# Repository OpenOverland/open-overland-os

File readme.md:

# ESP32-based control board

Custom designed control board build around ESP32-S3 module.

### Specification:

1. Board dimensions: 130 x 70 mm, 4x M3-mounting holes (3.2mm inner diameter);
2. XT30 header as main Power-input (up to 15 Amps);
3. Blade-fuse holder on the board (in light-green color);
4. Designed around ESP32-S3-WROOM-1U module (external antenna needs to be attached to its I-PEX/u.FL connector);
5. 2x 6-pin Molex MicroFit 3.0 headers for a connection with the Locks;
6. 1x 4-pin Molex MicroFit 3.0 header for a connection with the 12V-RGB LED-strip;
7. A bunch of Horizontaly-oriented external JST-type connectors for digital and analog inputs, CAN, and RFID-module;
8. A few Vertically-oriented internal JST-type connectors for UART and I2C interfaces;
9. Communication with the RFID-module is over SPI (RC522 module considered by default).

### Main features:

- Overcurrent, overvoltage, reverse polarity protection;
- ESP32-S3 as MCU with the in-built Wi-Fi and Bluetooth capabilities;
- Controls 2x LOCKs (Southco R4-EM-9P15-150);
- 4 digital inputs (2 at board's edge), protected (optical insulation);
- 2 analog inputs (1 at board's edge), protected (ESD);
- 12V input power indication;
- CAN-bus interface with the 120-Ohm termination jumper (at board's edge);
- On-board RFID-module connector (at board's edge);
- Additional CAN-interface with the 120-Ohms termination jumper;
- Internal headers for I2C and UART interfaces;
- Battery voltage measurement circuit
- Transformed 3.3V power indication;
- Automotive-grade power supply (peak voltages resistant);
- 4-pin Molex MicroFit 3.0 connector for Addressable RGB LED-strip (WS2815 type only - 12V)

-------------

### RC522 vs. PN532

**RC522**

`Pros`

Very inexpensive (about 5$/pcs.).
Excellent for MIFARE Classic applications.
Easy to use.
Low power consumption.

`Cons`

Primarily supports ISO14443A.
No NFC functionality.
*Shorter reading distance.*
Many low-cost modules use poorly tuned antennas, reducing performance.

**PN532**

`Pros`

Full-featured NFC controller.
Supports all three NFC operating modes:
RFID/NFC Reader
Card Emulation
Peer-to-Peer
Compatible with Android smartphones.
Supports a wider variety of RFID/NFC card types.
*Generally offers better sensitivity and longer read range.*
Most breakout boards allow selecting SPI, I²C, or UART via jumpers or switches.

`Cons`

More expensive (about 8$/pcs.).
Slightly more complex to integrate.
*Higher power consumption.*

-------------

### Version history

**v2a**
This version is designed for each door (2x locks only)

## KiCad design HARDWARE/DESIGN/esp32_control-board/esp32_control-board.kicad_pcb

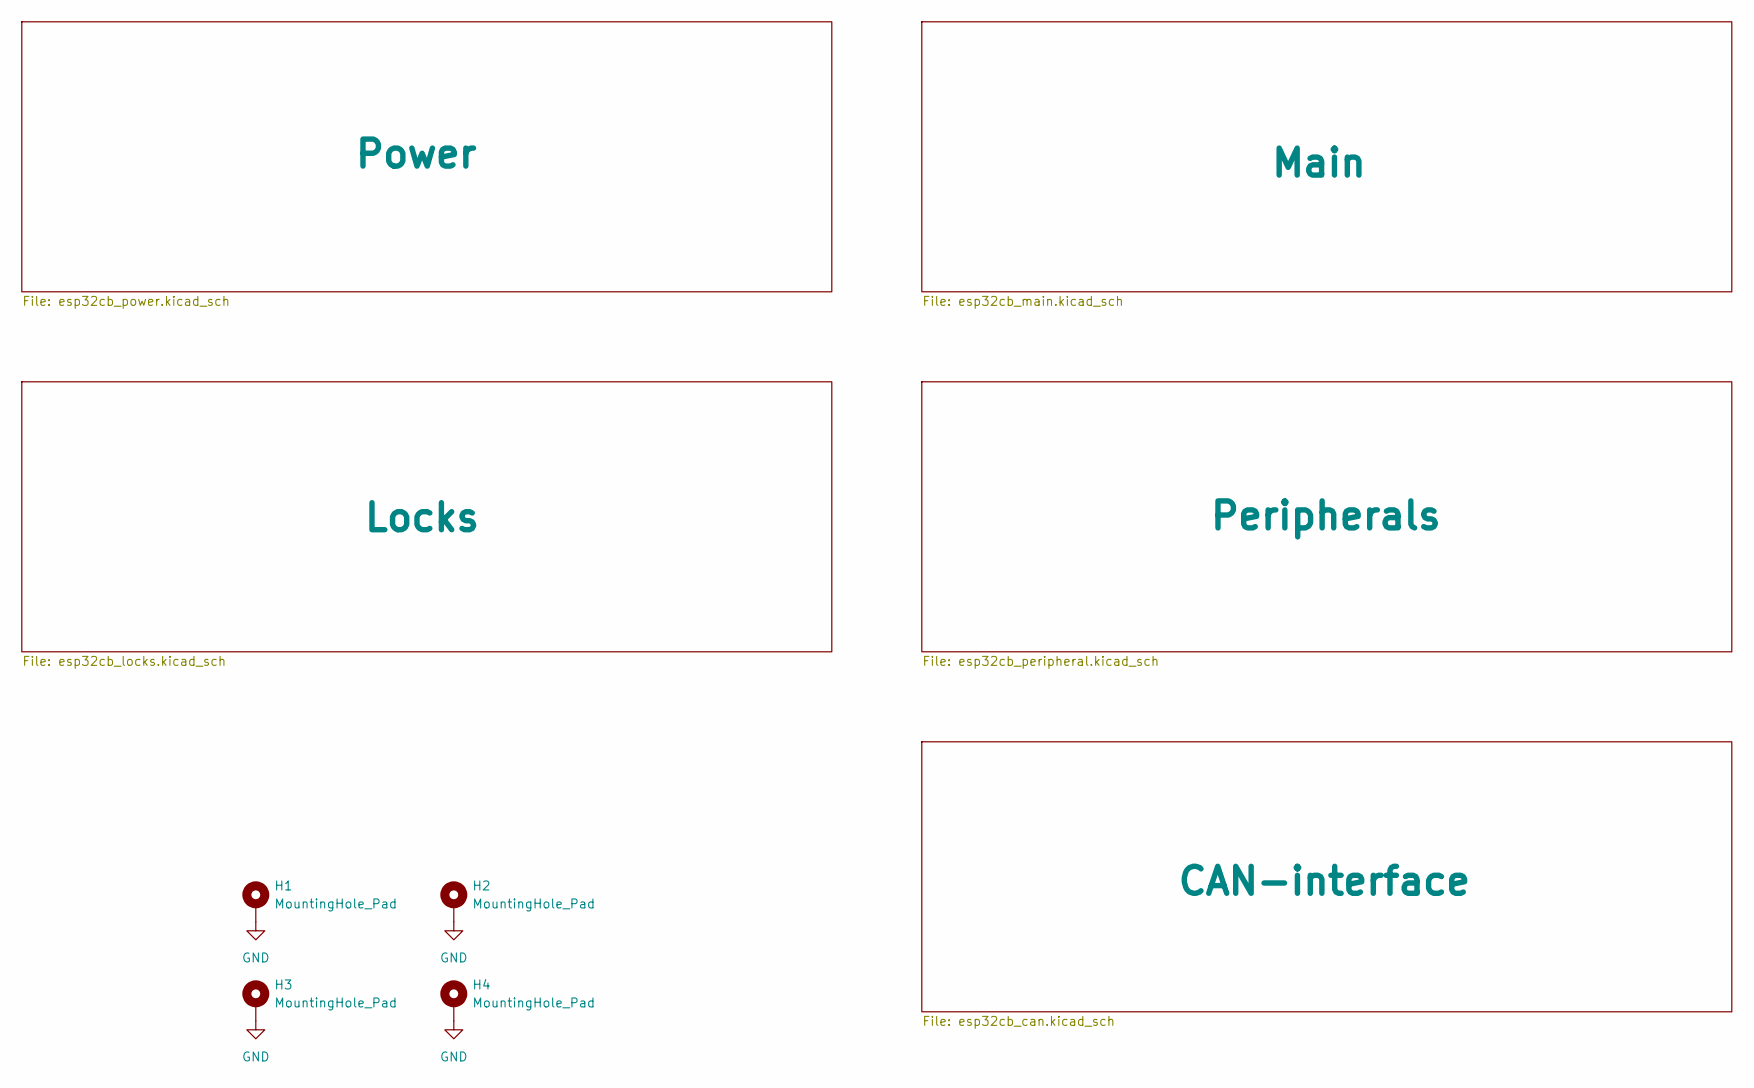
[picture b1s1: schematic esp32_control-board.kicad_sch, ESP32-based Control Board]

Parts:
H1, H2, H3, H4: MountingHole_Pad; MountingHole_3.2mm_M3_DIN965_Pad_TopBottom

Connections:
GND: H1.1 (1_1), H2.1 (1_1), H3.1 (1_1), H4.1 (1_1); also elsewhere on the board

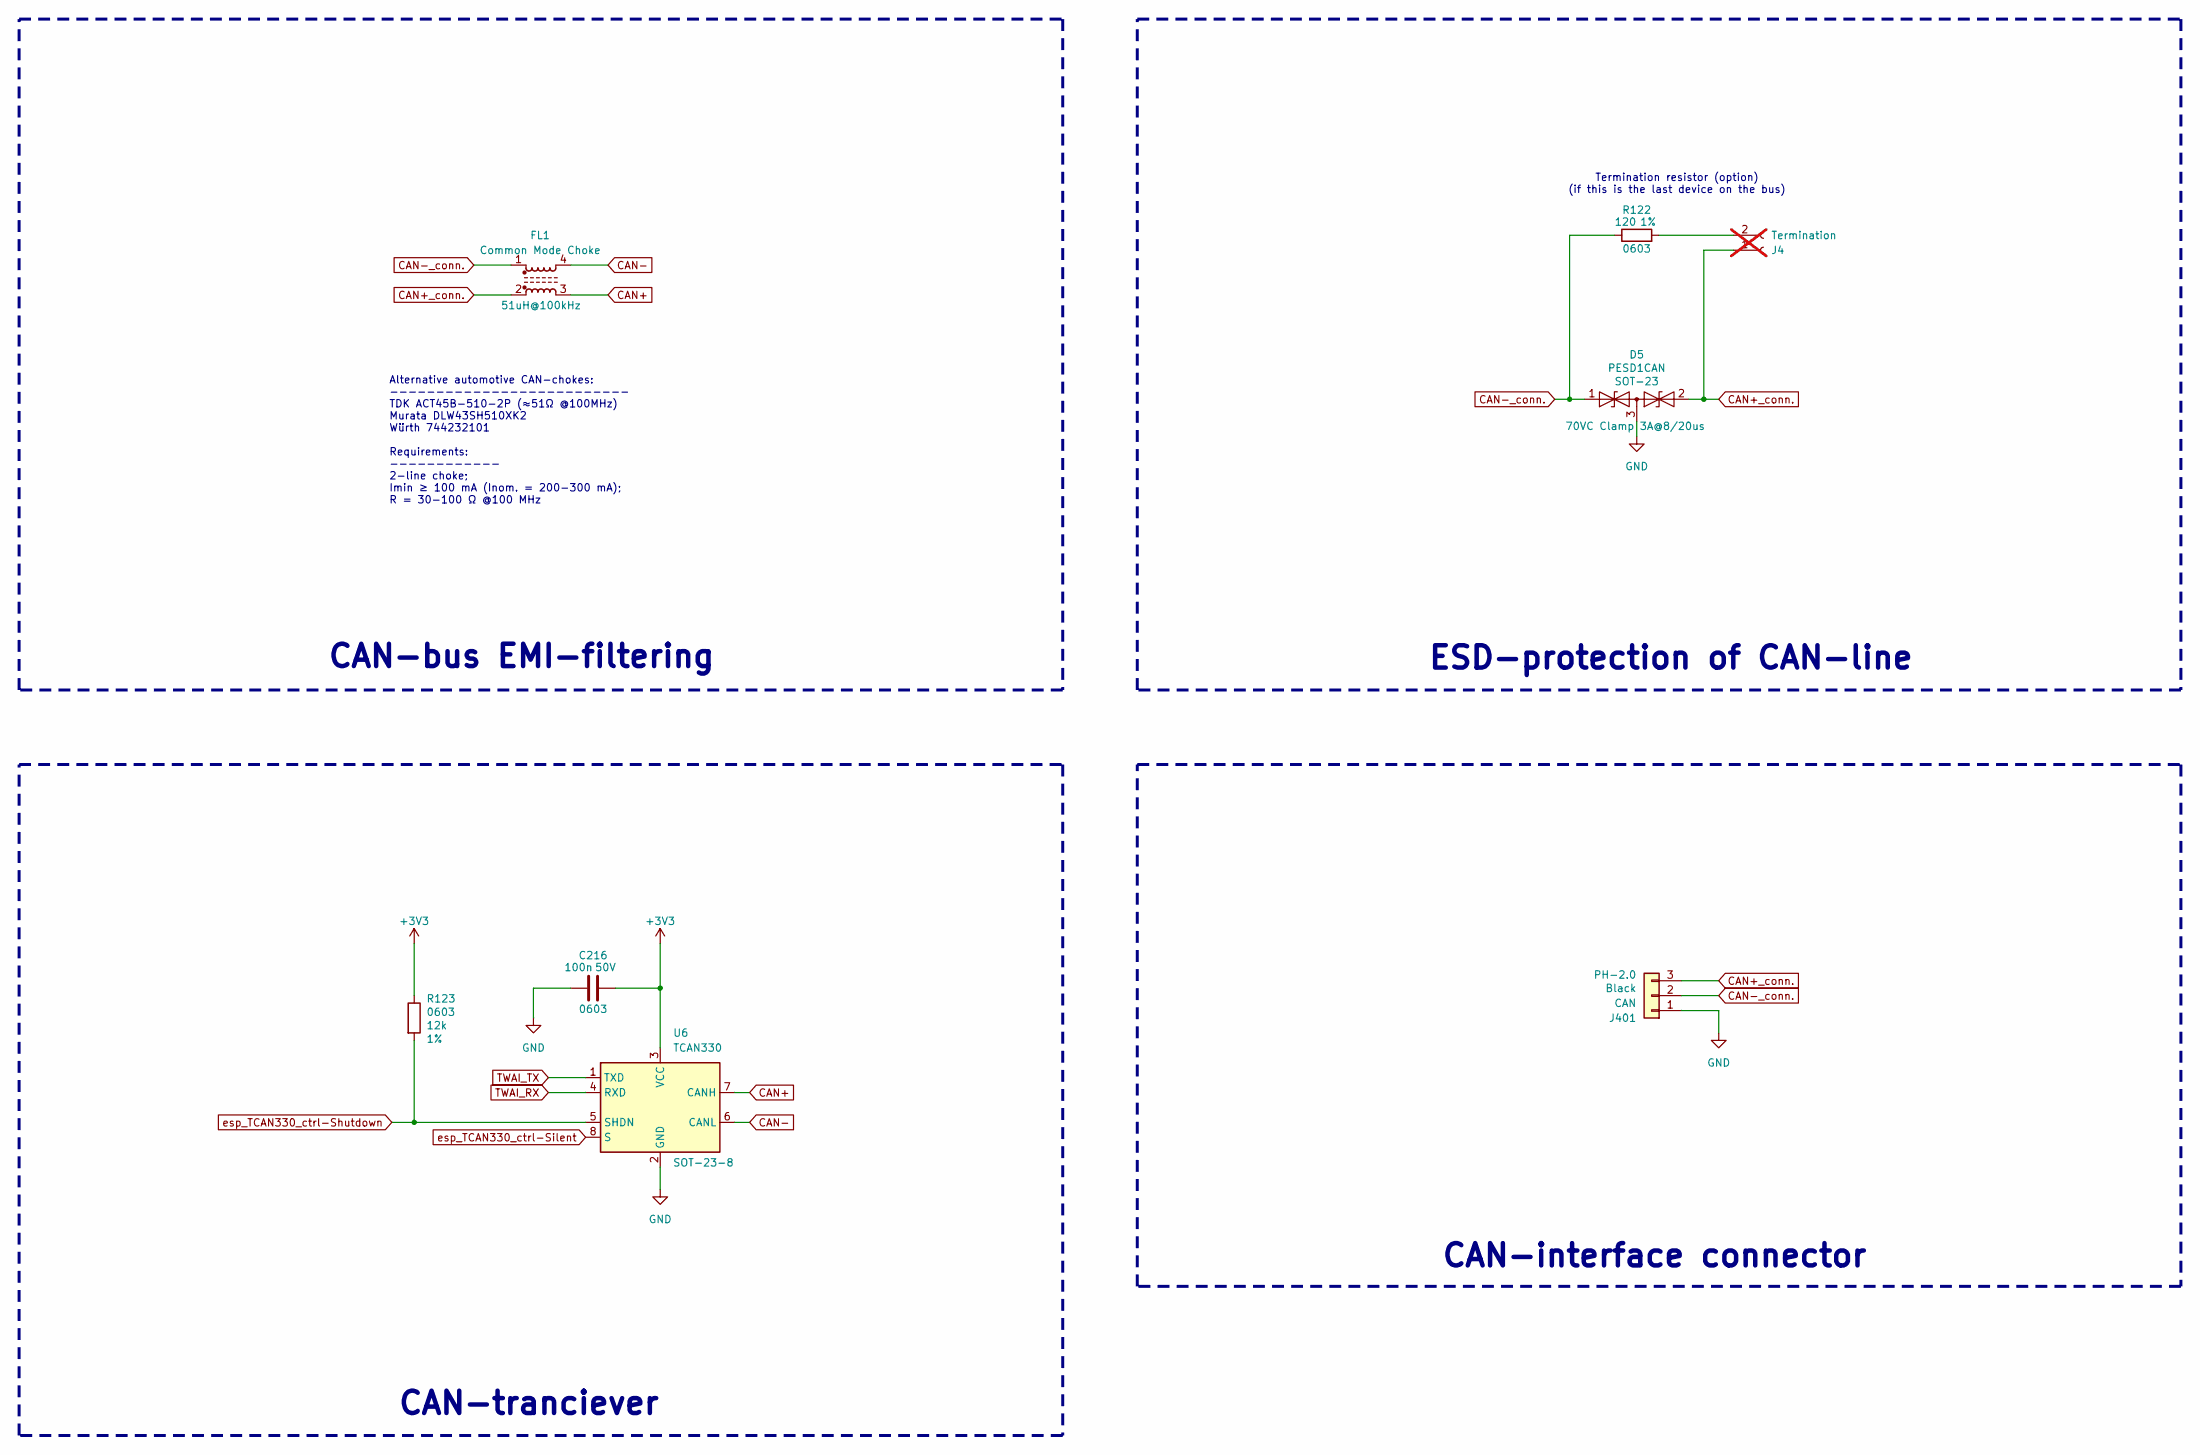
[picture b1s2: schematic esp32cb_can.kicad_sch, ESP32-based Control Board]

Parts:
C216: 100n; C_0603_1608Metric; LCSC part C1591
D5: PESD1CAN; SOT-23; LCSC part C15771
FL1: Common Mode Choke; C76584_IND-SMD_4P-L4.5-W3.2-TL; LCSC C76584
J4: Termination; PinHeader_1x02_P2.54mm_Horizontal; not fitted
J401: CAN; JST_PH_S3B-PH-K_1x03_P2.00mm_Horizontal
R122: 120; R_0603_1608Metric; LCSC C22787
R123: 12k; R_0603_1608Metric; LCSC C114659
U6: TCAN330; SOT-23-8; LCSC part C2877587

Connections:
+3V3: C216.2, R123.1, U6.3 (VCC); also elsewhere on the board
CAN+: FL1.3, U6.7 (CANH)
CAN+_conn.: D5.2 (A2), FL1.2, J4.1, J401.3
CAN-: FL1.4, U6.6 (CANL)
CAN-_conn.: D5.1 (A1), FL1.1, J401.2, R122.1
GND: C216.1, D5.3 (common), J401.1, U6.2 (GND); also elsewhere on the board
unnamed: J4.2, R122.2
TWAI_RX: U6.4 (RXD); also elsewhere on the board
TWAI_TX: U6.1 (TXD); also elsewhere on the board
esp_TCAN330_ctrl-Shutdown: R123.2, U6.5 (SHDN); also elsewhere on the board
esp_TCAN330_ctrl-Silent: U6.8 (S); also elsewhere on the board

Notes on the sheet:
CAN-tranciever
ESD-protection of CAN-line
CAN-interface connector
Alternative automotive CAN-chokes: -------------------------- TDK ACT45B-510-2P (≈51Ω @100MHz) Murata DLW43SH510XK2 Würth 744232101 Requirements: ------------ 2-line choke; Imin ≥ 100 mА (Inom. = 200-300 mА); R = 30-100 Ω @100 MHz
Termination resistor (option) (if this is the last device on the bus)
CAN-bus EMI-filtering

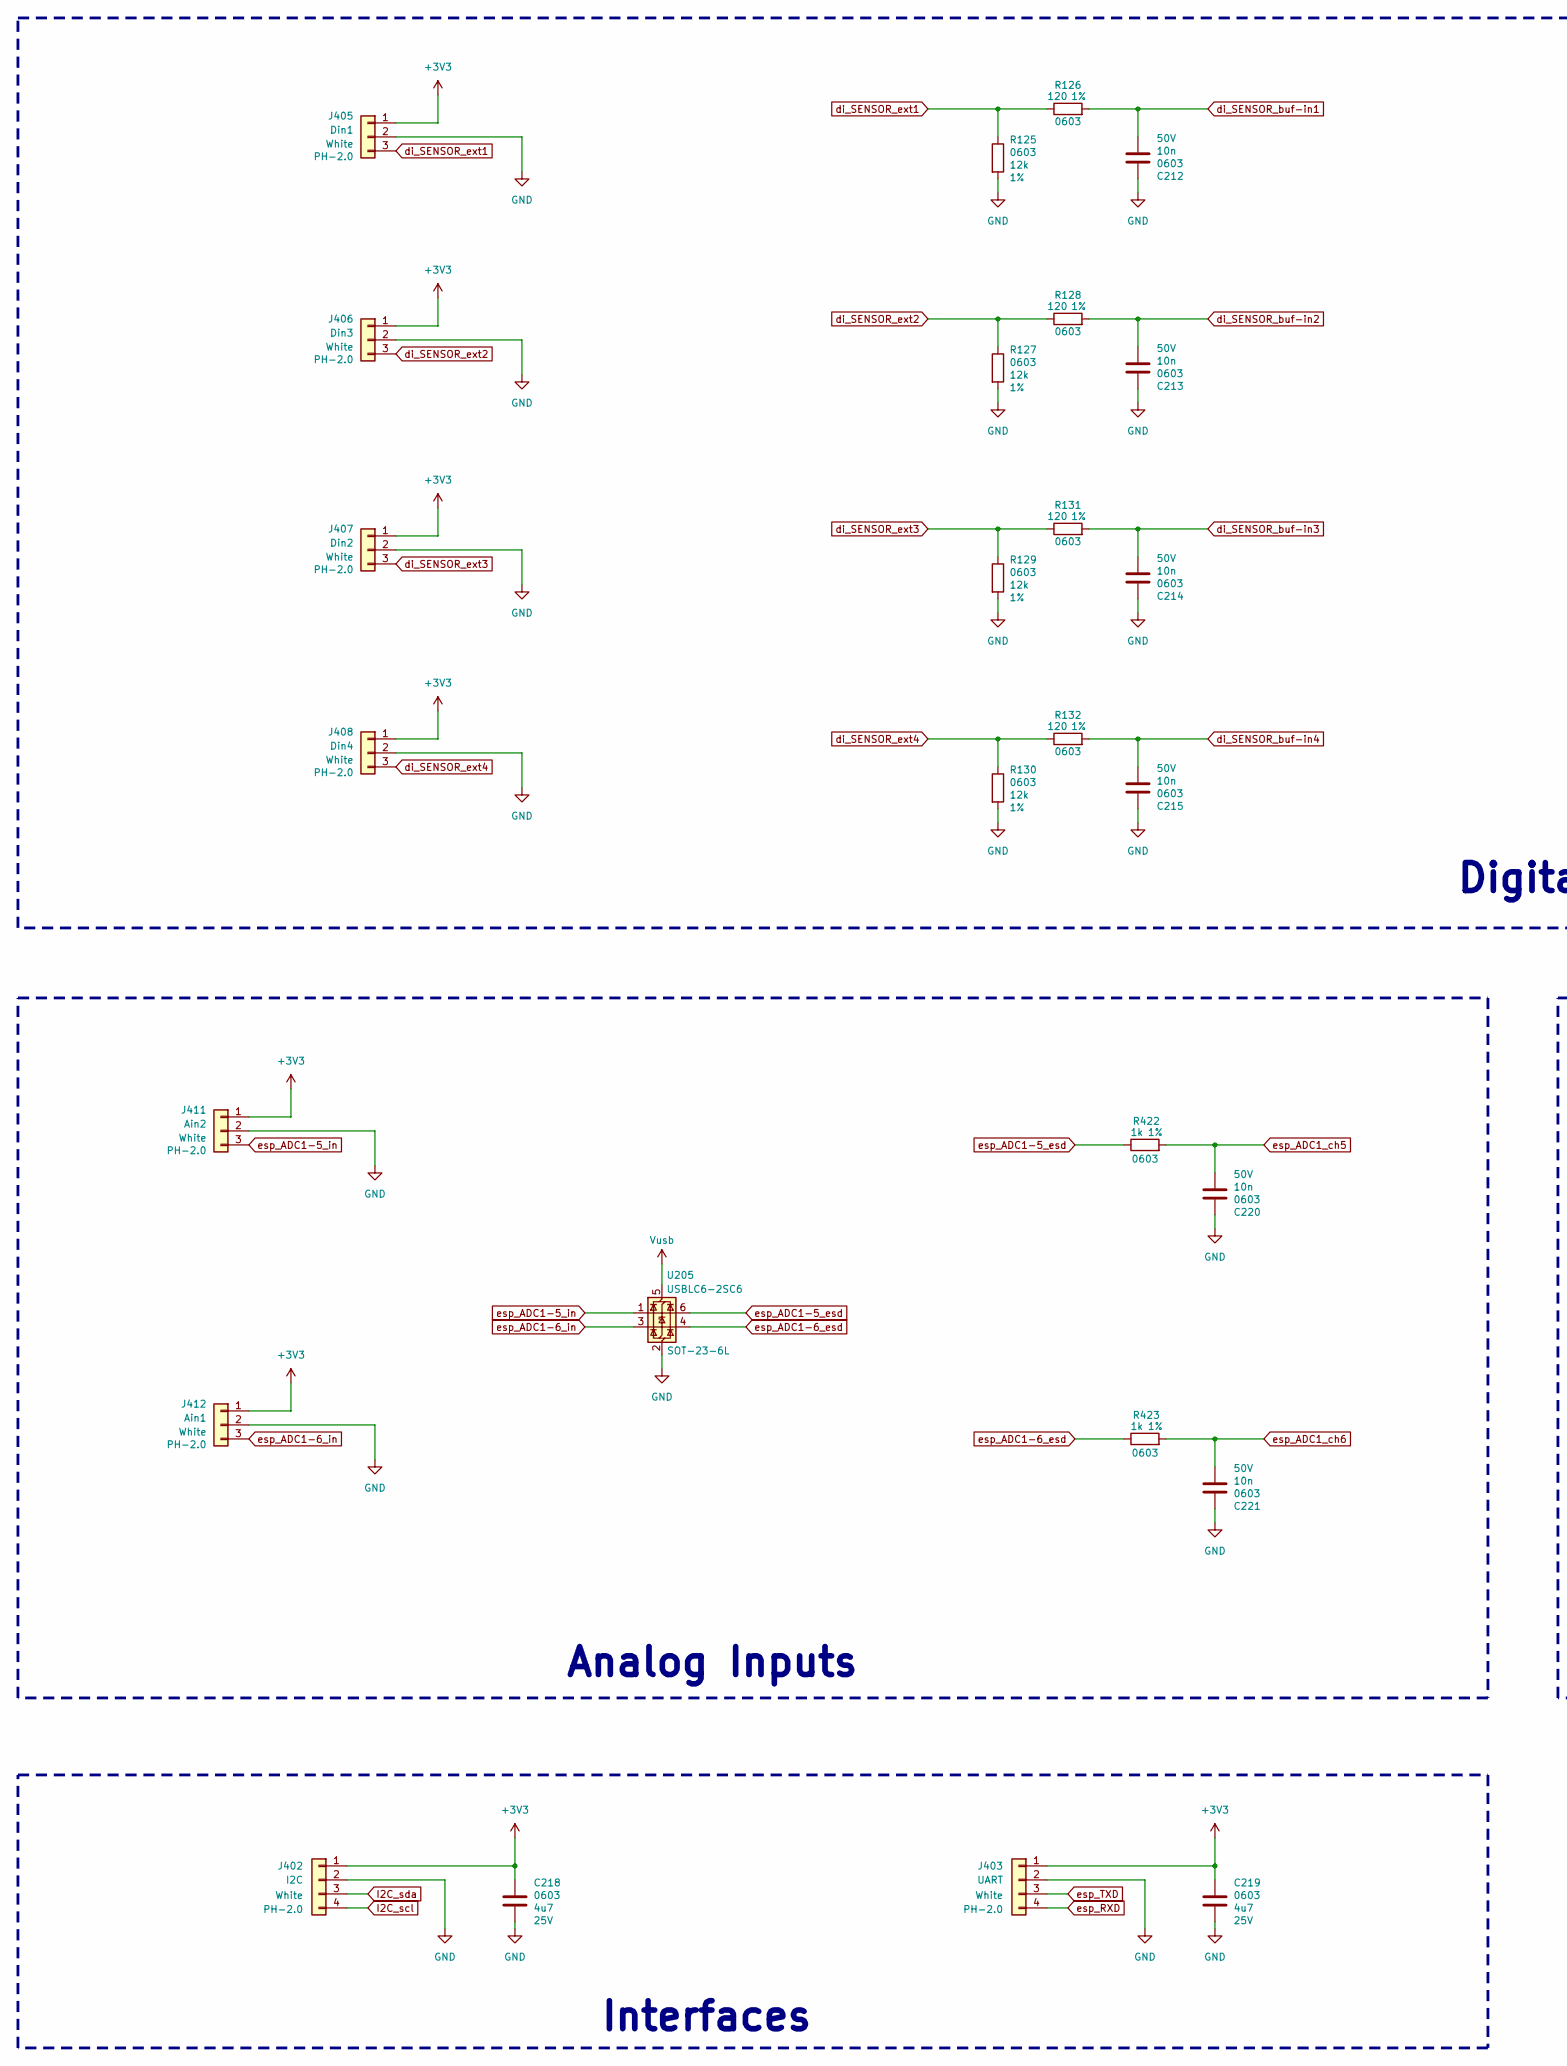
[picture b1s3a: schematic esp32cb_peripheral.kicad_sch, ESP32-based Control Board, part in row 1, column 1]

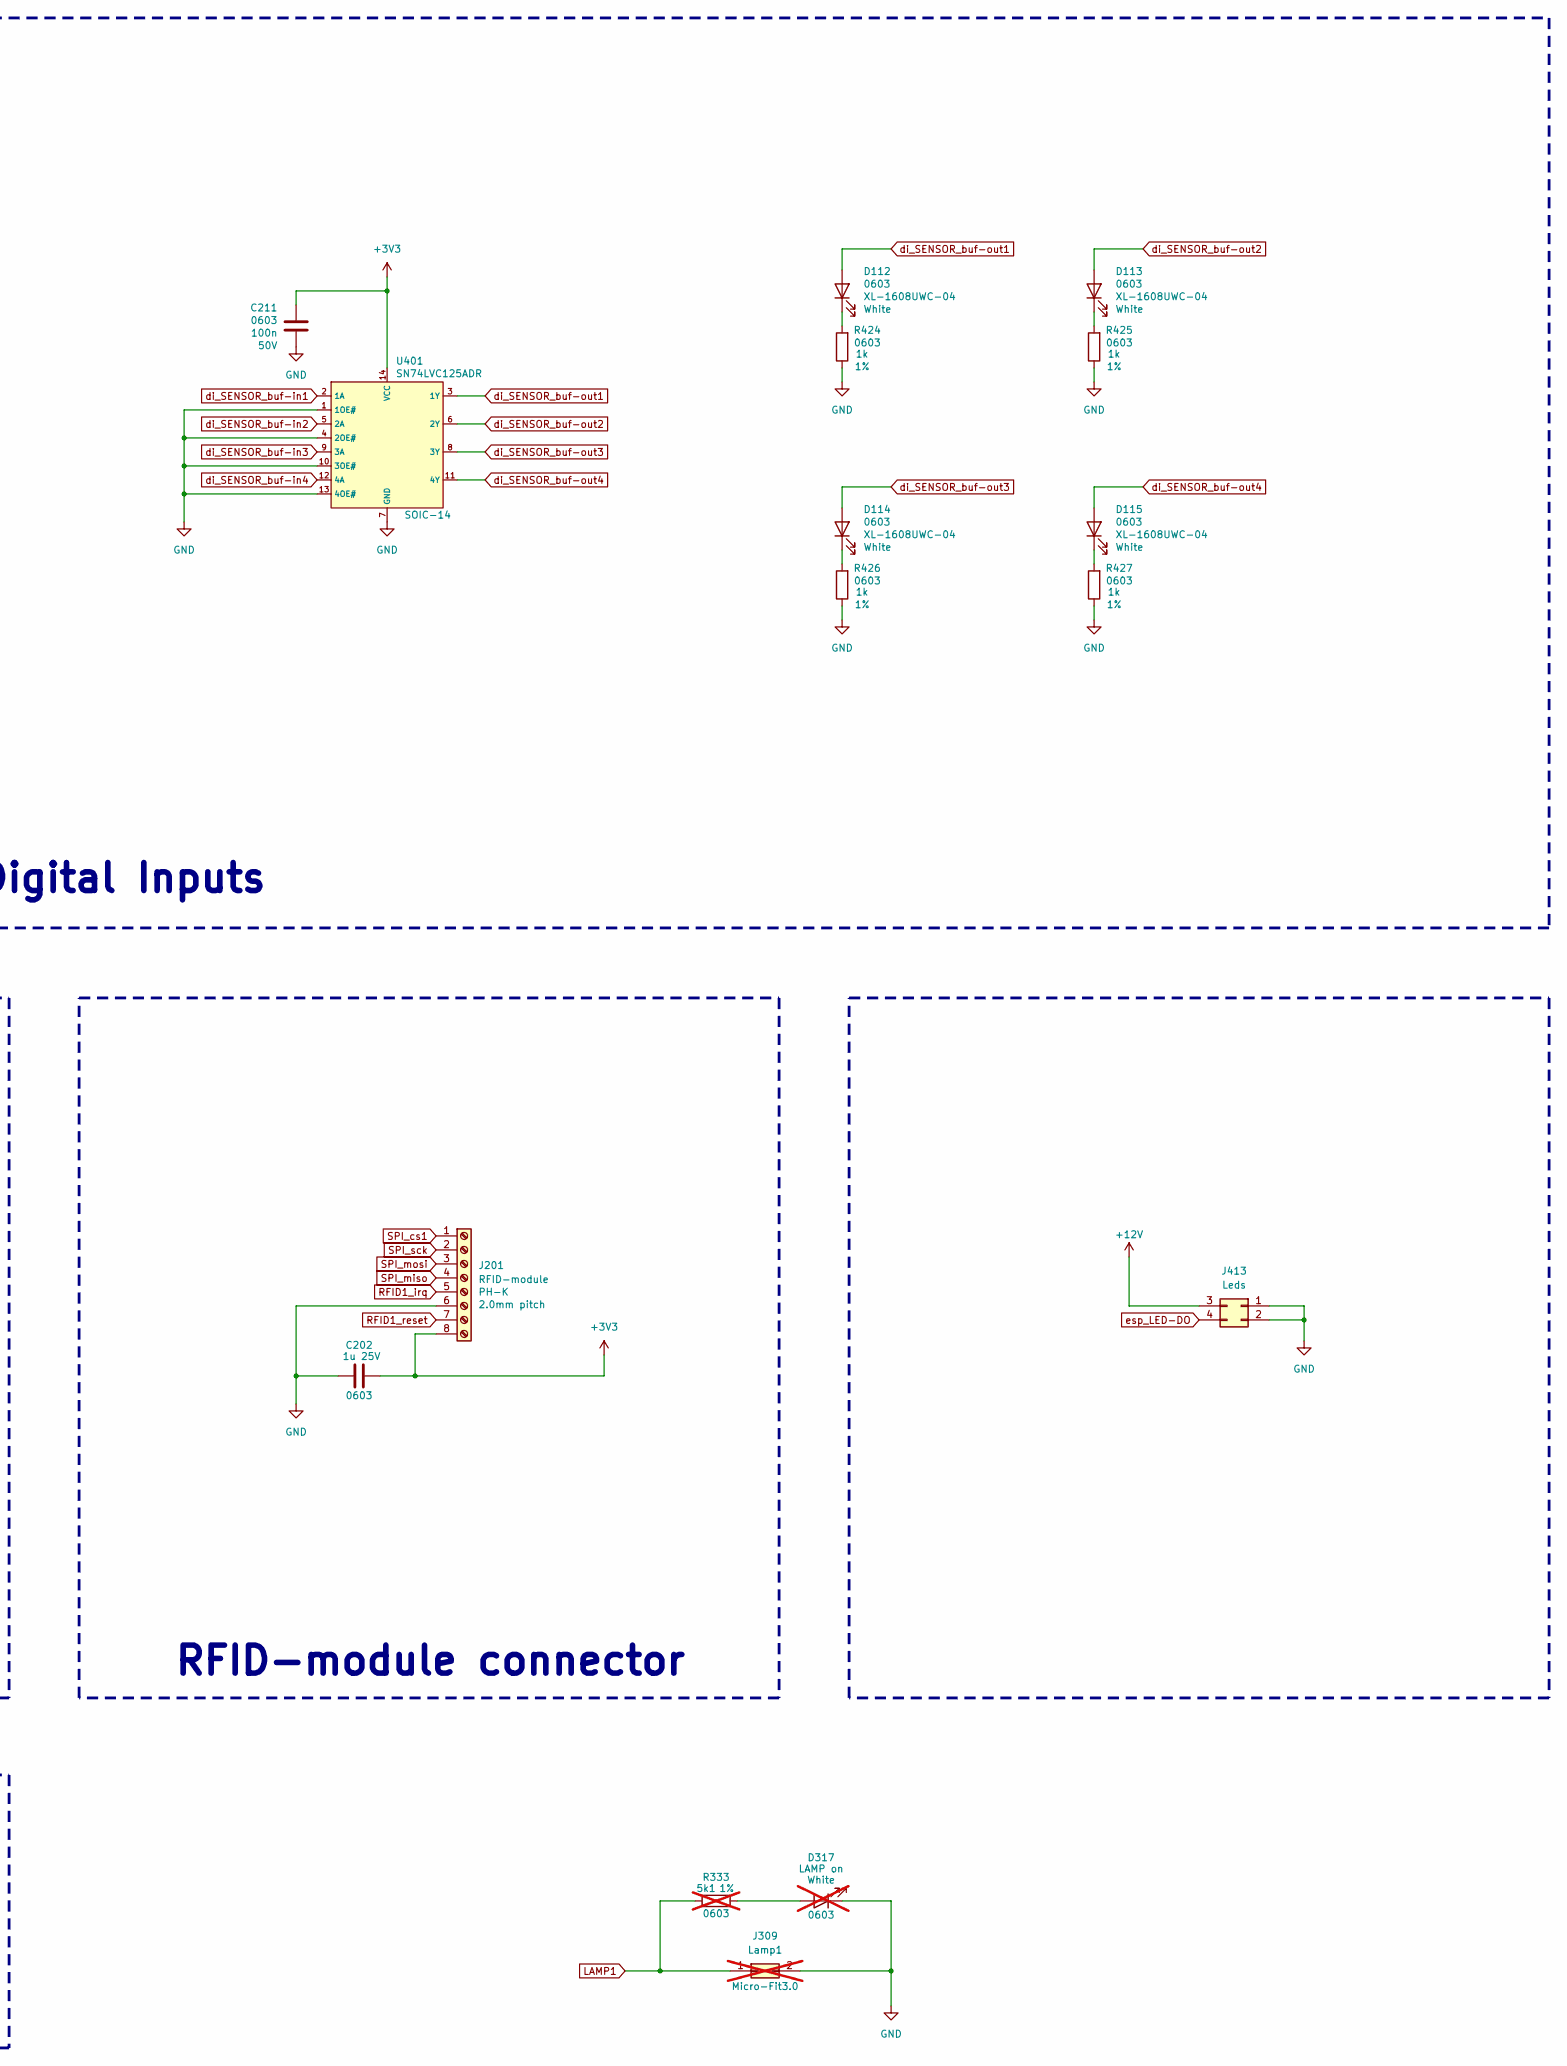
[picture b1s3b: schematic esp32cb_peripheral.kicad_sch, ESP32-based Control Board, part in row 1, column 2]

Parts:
C202: 1u; C_0603_1608Metric; LCSC part C29936
C211: 100n; C_0603_1608Metric; LCSC part C1591
C212, C213, C214, C215, C220, C221: 10n; C_0603_1608Metric; LCSC C1589
C218, C219: 4u7; C_0805_2012Metric; LCSC C98195
D112, D113, D114, D115: XL-1608UWC-04; LED_0603_1608Metric; LCSC part C965808
D317: LAMP on; LED_0603_1608Metric; LCSC C965808; not fitted
J201: RFID-module; JST_PH_S8B-PH-K_1x08_P2.00mm_Horizontal; LCSC C157974
J309: Lamp1; Molex_Micro-Fit_3.0_43045-0200_2x01_P3.00mm_Horizontal; LCSC C122431; not fitted
J402: I2C; JST_PH_B4B-PH-K_1x04_P2.00mm_Vertical; LCSC C131334
J403: UART; JST_PH_B4B-PH-K_1x04_P2.00mm_Vertical; LCSC C131334
J405: Din1; JST_PH_S3B-PH-K_1x03_P2.00mm_Horizontal
J406: Din3; JST_PH_B3B-PH-K_1x03_P2.00mm_Vertical; LCSC C131339
J407: Din2; JST_PH_S3B-PH-K_1x03_P2.00mm_Horizontal
J408: Din4; JST_PH_B3B-PH-K_1x03_P2.00mm_Vertical; LCSC C131339
J411: Ain2; JST_PH_B3B-PH-K_1x03_P2.00mm_Vertical; LCSC C131339
J412: Ain1; JST_PH_S3B-PH-K_1x03_P2.00mm_Horizontal
J413: Leds; Molex_Micro-Fit_3.0_43045-0400_2x02_P3.00mm_Horizontal; LCSC C122413
R125, R127, R129, R130: 12k; R_0603_1608Metric; LCSC C114659
R126, R128, R131, R132: 120; R_0603_1608Metric; LCSC C22787
R333: 5k1; R_0603_1608Metric; LCSC part C2907044; not fitted
R422, R423, R424, R425, R426, R427: 1k; R_0603_1608Metric; LCSC part C21190
U205: USBLC6-2SC6; SOT-23-6; LCSC part C7519
U401: SN74LVC125ADR; SOIC-14_3.9x8.7mm_P1.27mm; LCSC C7661

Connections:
+3V3: C202.1, C211.2, C218.2, C219.2, J201.8, J402.1, J403.1, J405.1, J406.1, J407.1, J408.1, J411.1, J412.1, U401.14 (VCC); also elsewhere on the board
+12V: J413.3; also elsewhere on the board
GND: C202.2, C211.1, C212.2, C213.2, C214.2, C215.2, C218.1, C219.1, C220.2, C221.2, D317.1 (K), J201.6, J309.2, J402.2, J403.2, J405.2, J406.2, J407.2, J408.2, J411.2, J412.2, J413.1, J413.2, R125.2, R127.2, R129.2, R130.2, R424.1, R425.1, R426.1, R427.1, U205.2 (GND), U401.1 (1OE#), U401.4 (2OE#), U401.7 (GND), U401.10 (3OE#), U401.13 (4OE#); also elsewhere on the board
I2C_scl: J402.4; also elsewhere on the board
I2C_sda: J402.3; also elsewhere on the board
unnamed: D112.1 (K), R424.2
unnamed: D113.1 (K), R425.2
unnamed: D114.1 (K), R426.2
unnamed: D115.1 (K), R427.2
unnamed: D317.2 (A), R333.1
unnamed: J309.1, R333.2
RFID1_irq: J201.5; also elsewhere on the board
RFID1_reset: J201.7; also elsewhere on the board
SPI_cs1: J201.1; also elsewhere on the board
SPI_miso: J201.4; also elsewhere on the board
SPI_mosi: J201.3; also elsewhere on the board
SPI_sck: J201.2; also elsewhere on the board
Vusb: U205.5 (VBUS); also elsewhere on the board
di_SENSOR_buf-in1: C212.1, R126.2, U401.2 (1A)
di_SENSOR_buf-in2: C213.1, R128.2, U401.5 (2A)
di_SENSOR_buf-in3: C214.1, R131.2, U401.9 (3A)
di_SENSOR_buf-in4: C215.1, R132.2, U401.12 (4A)
di_SENSOR_buf-out1: D112.2 (A), U401.3 (1Y)
di_SENSOR_buf-out2: D113.2 (A), U401.6 (2Y)
di_SENSOR_buf-out3: D114.2 (A), U401.8 (3Y)
di_SENSOR_buf-out4: D115.2 (A), U401.11 (4Y)
di_SENSOR_ext1: J405.3, R125.1, R126.1
di_SENSOR_ext2: J406.3, R127.1, R128.1
di_SENSOR_ext3: J407.3, R129.1, R131.1
di_SENSOR_ext4: J408.3, R130.1, R132.1
esp_ADC1-5_esd: R422.1, U205.6 (I/O1)
esp_ADC1-5_in: J411.3, U205.1 (I/O1)
esp_ADC1-6_esd: R423.1, U205.4 (I/O2)
esp_ADC1-6_in: J412.3, U205.3 (I/O2)
esp_ADC1_ch5: C220.1, R422.2; also elsewhere on the board
esp_ADC1_ch6: C221.1, R423.2; also elsewhere on the board
esp_LED-DO: J413.4; also elsewhere on the board
esp_RXD: J403.4; also elsewhere on the board
esp_TXD: J403.3; also elsewhere on the board

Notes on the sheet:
Interfaces
Analog Inputs
RFID-module connector
Digital Inputs

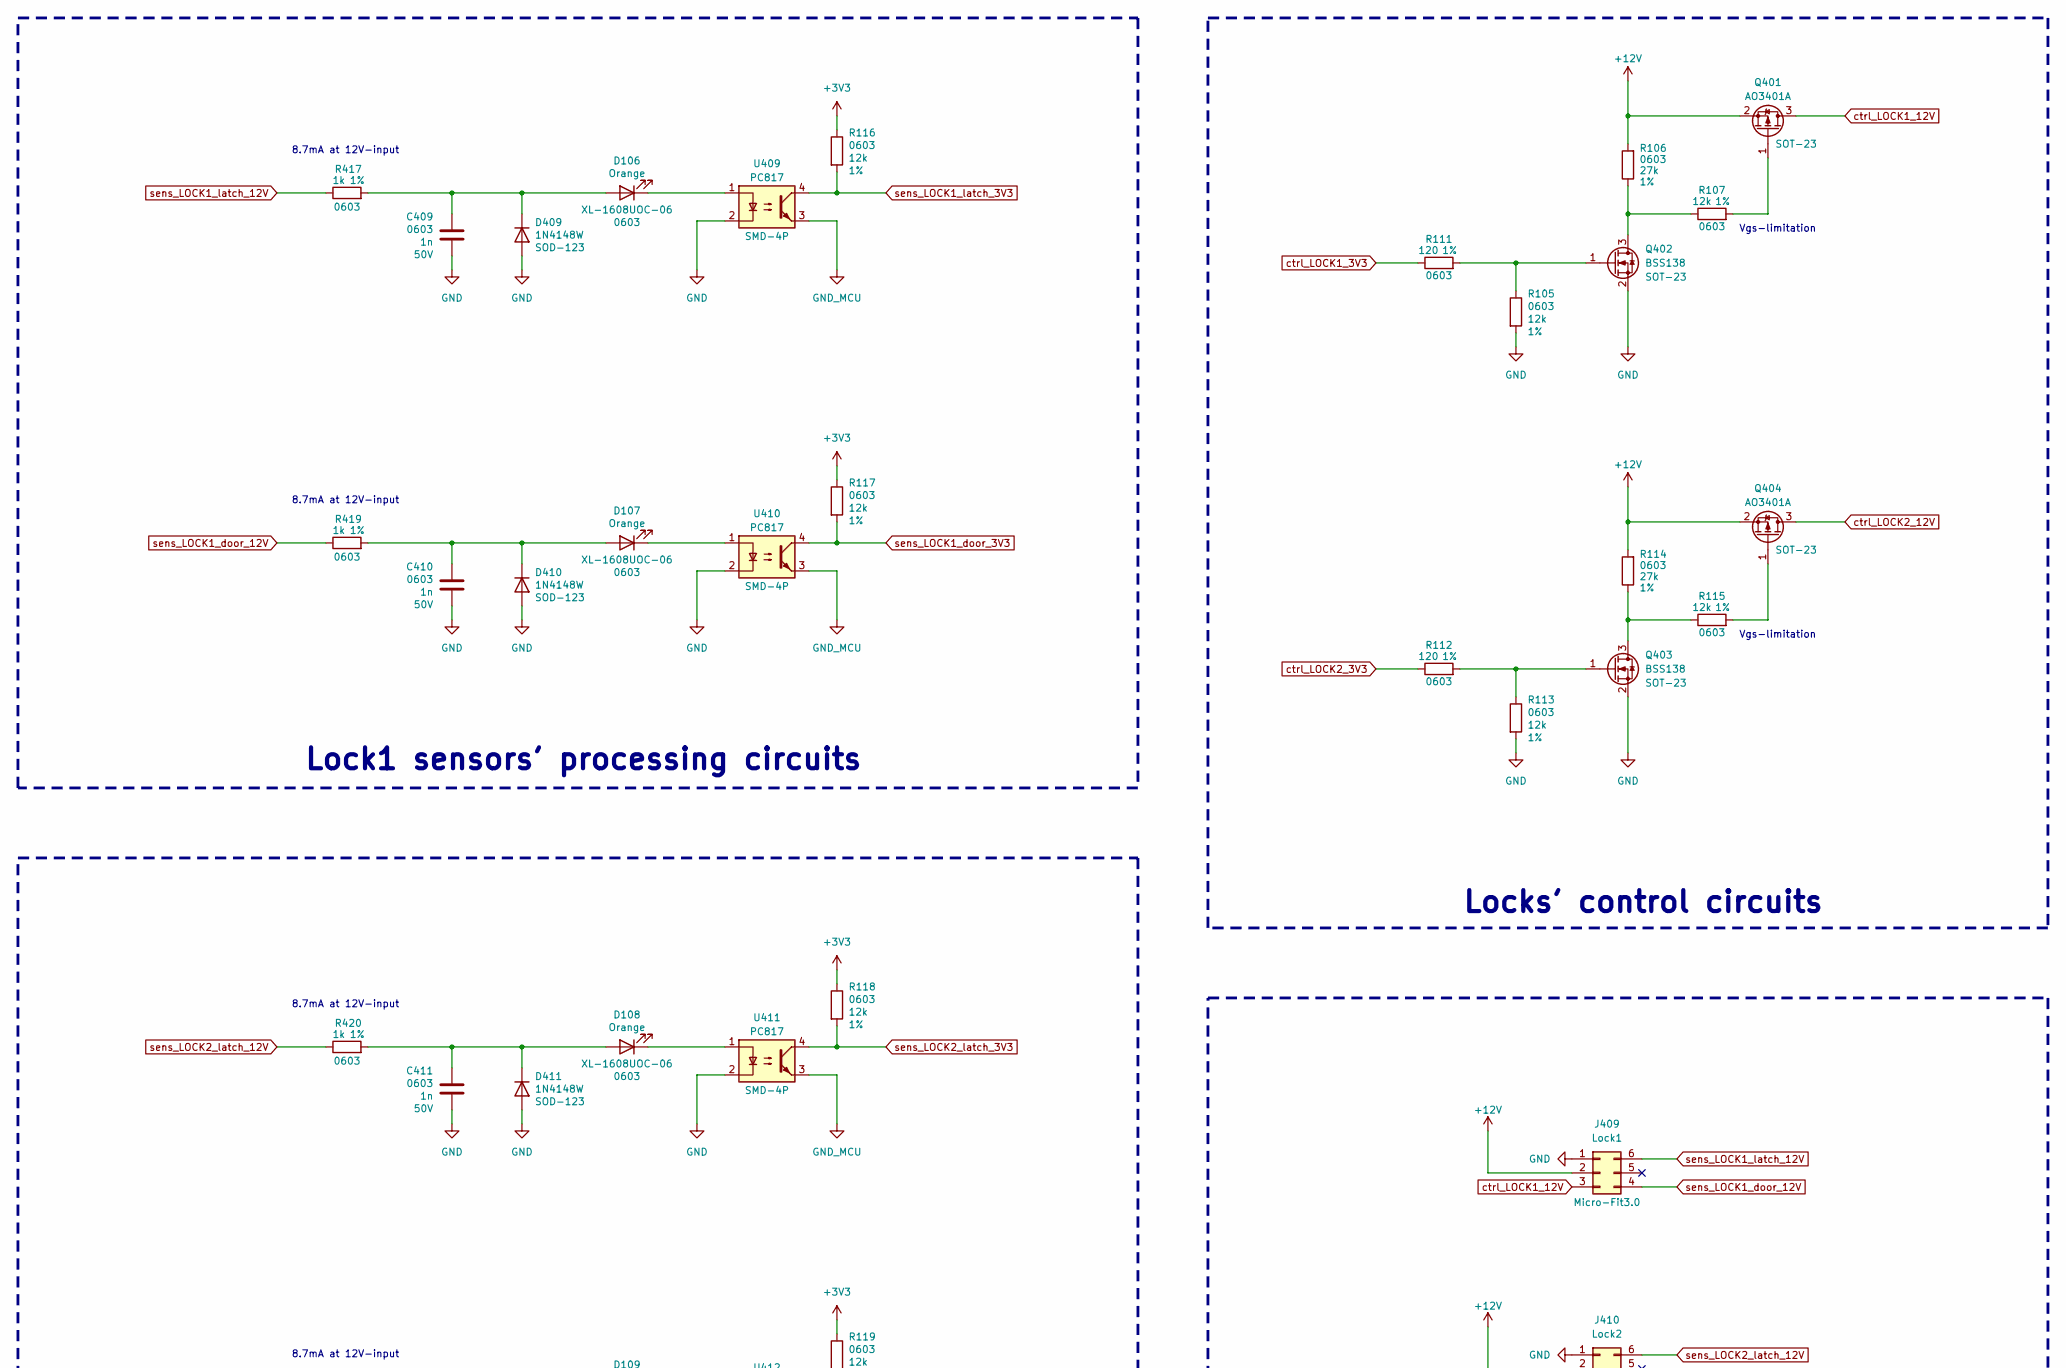
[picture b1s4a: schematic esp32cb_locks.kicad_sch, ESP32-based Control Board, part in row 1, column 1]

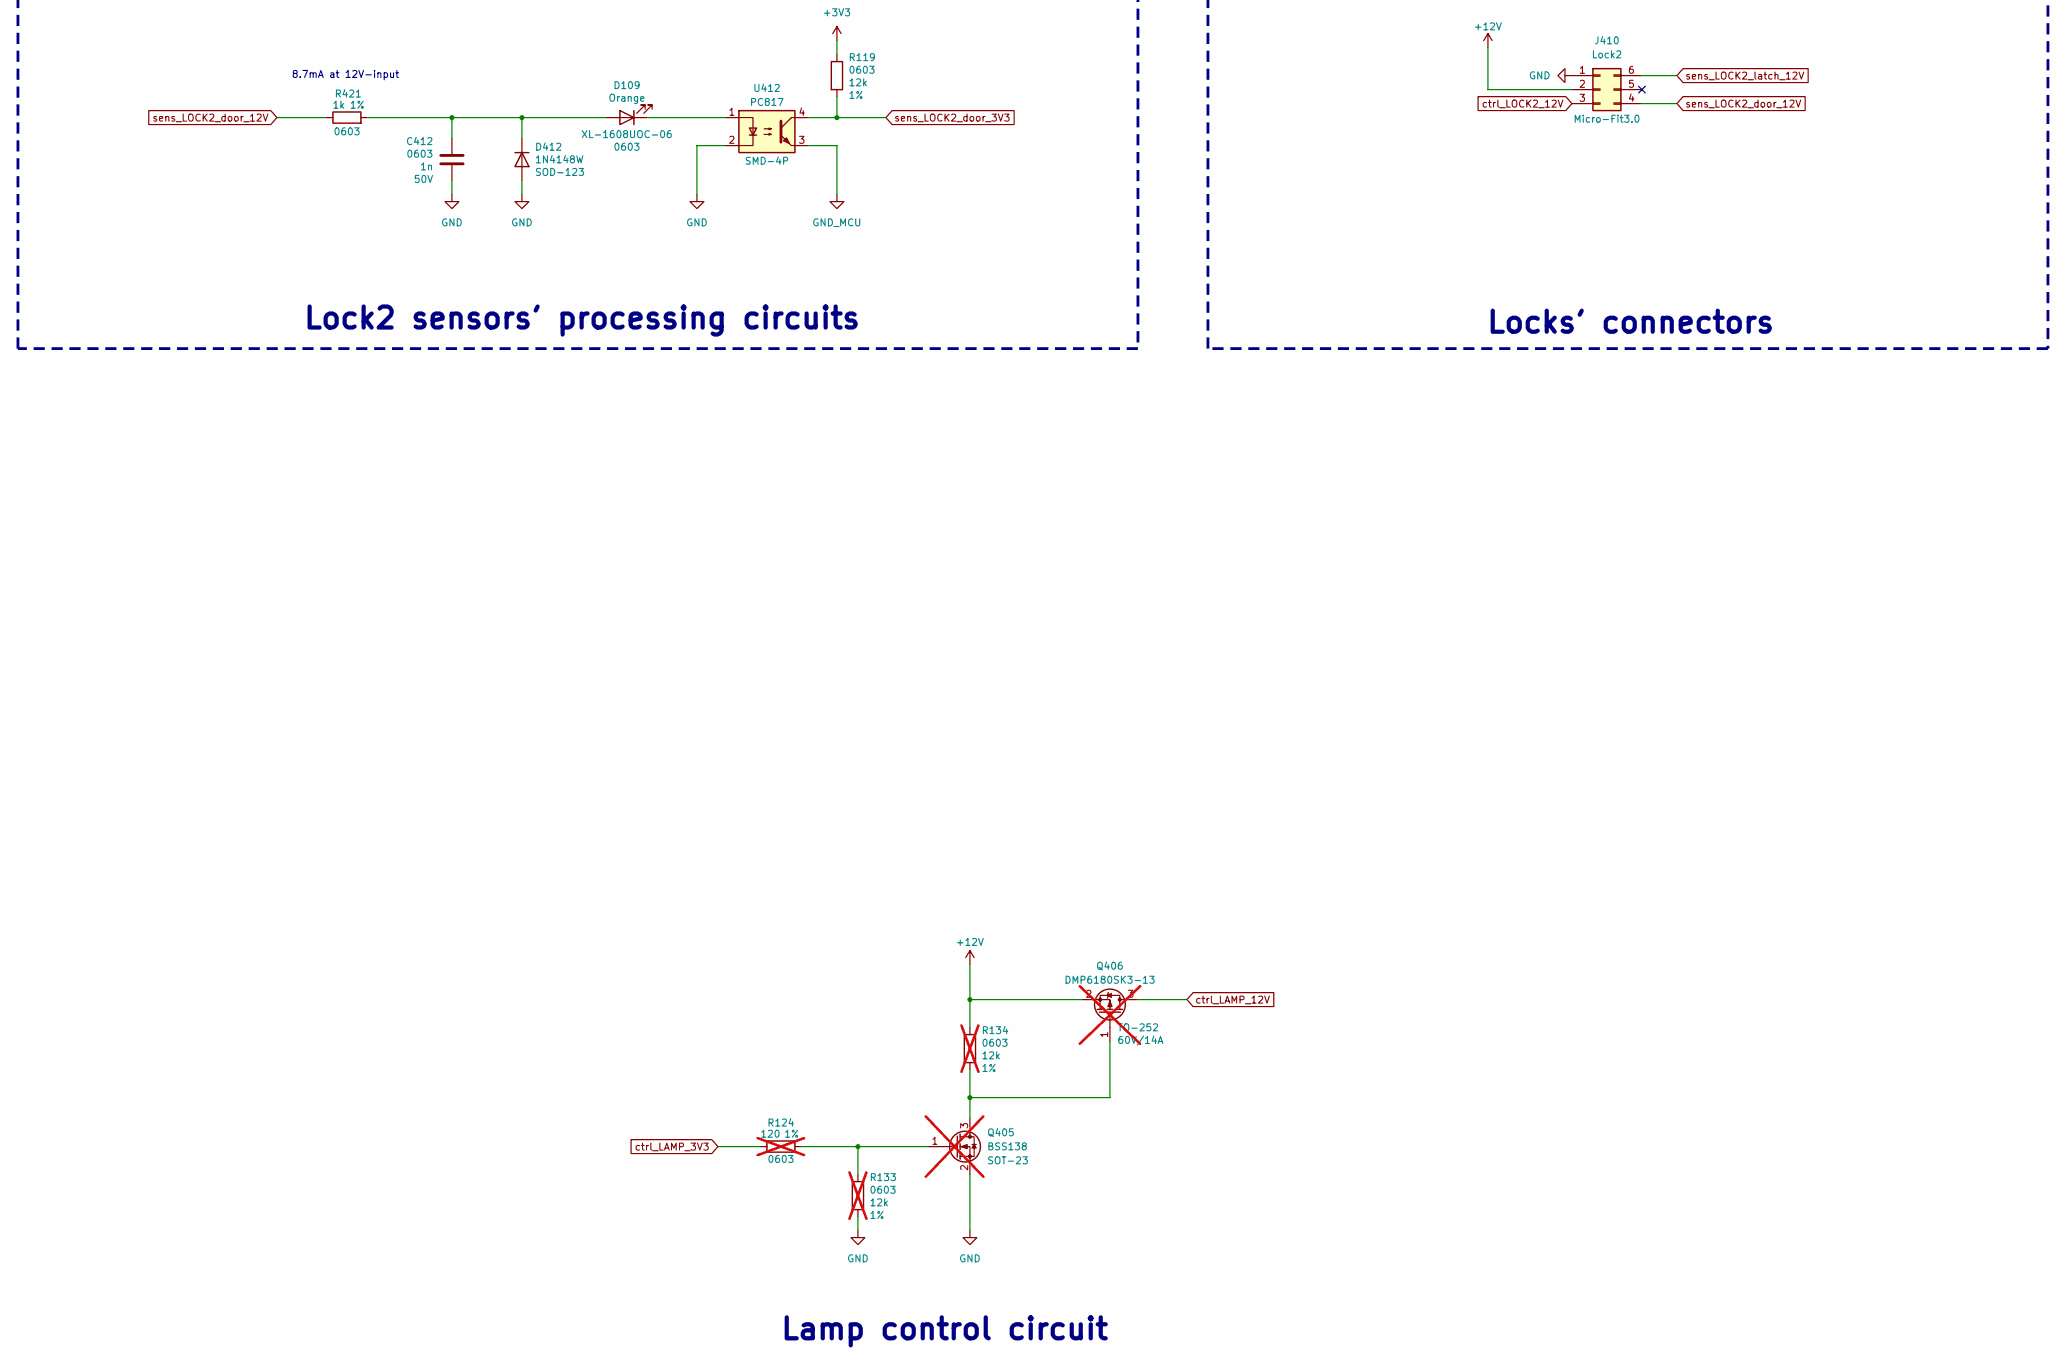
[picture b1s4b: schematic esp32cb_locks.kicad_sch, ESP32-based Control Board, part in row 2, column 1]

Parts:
C409, C410, C411, C412: 1n; C_0603_1608Metric; LCSC C106246
D106, D107, D108, D109: XL-1608UOC-06; LED_0603_1608Metric; LCSC C965800
D409, D410, D411, D412: 1N4148W; D_SOD-123; LCSC C917030
J409: Lock1; Molex_Micro-Fit_3.0_43045-0600_2x03_P3.00mm_Horizontal; LCSC C127367
J410: Lock2; Molex_Micro-Fit_3.0_43045-0600_2x03_P3.00mm_Horizontal; LCSC C127367
Q401, Q404: AO3401A; SOT-23; LCSC C2938368
Q402, Q403: BSS138; SOT-23; LCSC C52895
Q405: BSS138; SOT-23; LCSC C52895; not fitted
Q406: DMP6180SK3-13; TO-252-2; LCSC C93034; not fitted
R105, R107, R113, R115, R116, R117, R118, R119: 12k; R_0603_1608Metric; LCSC C114659
R106, R114: 27k; R_0603_1608Metric; LCSC C114614
R111, R112: 120; R_0603_1608Metric; LCSC C22787
R124: 120; R_0603_1608Metric; LCSC C22787; not fitted
R133, R134: 12k; R_0603_1608Metric; LCSC C114659; not fitted
R417, R419, R420, R421: 1k; R_0603_1608Metric; LCSC part C21190
U409, U410, U411, U412: PC817; DIP-4_W7.62mm_SMDSocket_SmallPads; LCSC C66405

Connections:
+3V3: R116.1, R117.1, R118.1, R119.1; also elsewhere on the board
+12V: J409.2, J410.2, Q401.2 (S), Q404.2 (S), Q406.2 (S), R106.2, R114.2, R134.1; also elsewhere on the board
GND: C409.1, C410.1, C411.1, C412.1, D409.2 (A), D410.2 (A), D411.2 (A), D412.2 (A), J409.1, J410.1, Q402.2 (S), Q403.2 (S), Q405.2 (S), R105.2, R113.2, R133.2, U409.2, U410.2, U411.2, U412.2; also elsewhere on the board
GND_MCU: U409.3, U410.3, U411.3, U412.3; also elsewhere on the board
unnamed: C409.2, D106.2 (A), D409.1 (K), R417.2
unnamed: D106.1 (K), U409.1
unnamed: C410.2, D107.2 (A), D410.1 (K), R419.2
unnamed: D107.1 (K), U410.1
unnamed: C411.2, D108.2 (A), D411.1 (K), R420.2
unnamed: D108.1 (K), U411.1
unnamed: C412.2, D109.2 (A), D412.1 (K), R421.2
unnamed: D109.1 (K), U412.1
unnamed: Q401.1 (G), R107.2
unnamed: Q402.3 (D), R106.1, R107.1
unnamed: Q402.1 (G), R105.1, R111.2
unnamed: Q403.3 (D), R114.1, R115.1
unnamed: Q403.1 (G), R112.2, R113.1
unnamed: Q404.1 (G), R115.2
unnamed: Q405.1 (G), R124.2, R133.1
unnamed: Q405.3 (D), Q406.1 (G), R134.2
ctrl_LOCK1_3V3: R111.1; also elsewhere on the board
ctrl_LOCK1_12V: J409.3, Q401.3 (D)
ctrl_LOCK2_3V3: R112.1; also elsewhere on the board
ctrl_LOCK2_12V: J410.3, Q404.3 (D)
sens_LOCK1_door_3V3: R117.2, U410.4; also elsewhere on the board
sens_LOCK1_door_12V: J409.4, R419.1
sens_LOCK1_latch_3V3: R116.2, U409.4; also elsewhere on the board
sens_LOCK1_latch_12V: J409.6, R417.1
sens_LOCK2_door_3V3: R119.2, U412.4; also elsewhere on the board
sens_LOCK2_door_12V: J410.4, R421.1
sens_LOCK2_latch_3V3: R118.2, U411.4; also elsewhere on the board
sens_LOCK2_latch_12V: J410.6, R420.1

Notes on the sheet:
Vgs-limitation
8.7mA at 12V-input
Locks' control circuits
Locks' connectors
Lock1 sensors' processing circuits
Lock2 sensors' processing circuits
Lamp control circuit
